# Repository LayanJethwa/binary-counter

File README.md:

# binary-counter

This is a controller board with 3 keys and 3 LEDs, the LEDs display a number from 0-7 in binary, the left key decrements, right key increments, and top key resets the counter.

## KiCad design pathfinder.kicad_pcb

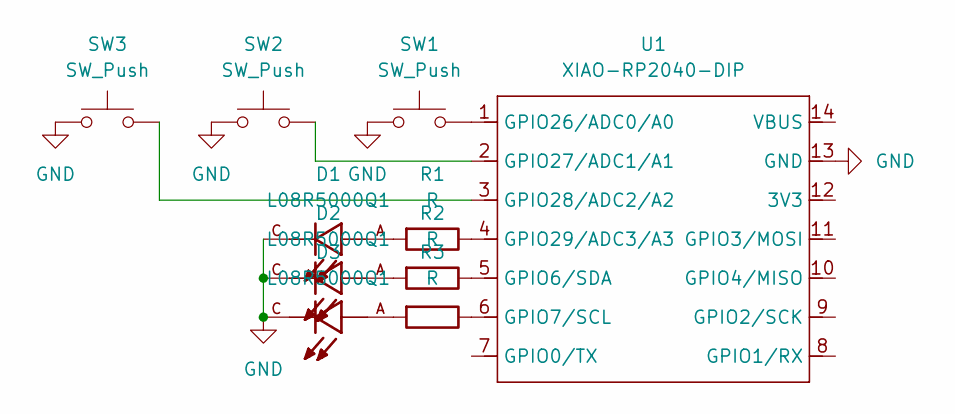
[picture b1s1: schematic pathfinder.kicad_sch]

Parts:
D1, D2, D3: L08R5000Q1; LEDRD254W57D500H1070; PARTREV NA
R1, R2, R3: R; R_Axial_DIN0204_L3.6mm_D1.6mm_P5.08mm_Horizontal
SW1, SW2, SW3: SW_Push; SW_Cherry_MX_1.00u_PCB
U1: XIAO-RP2040-DIP

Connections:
GND: D1.C, D2.C, D3.C, SW1.1, SW2.1, SW3.1, U1.13 (GND)
unnamed: D1.A, R1.2
unnamed: D2.A, R2.2
unnamed: D3.A, R3.2
unnamed: R2.1, U1.5 (GPIO6/SDA)
unnamed: R3.1, U1.6 (GPIO7/SCL)
unnamed: SW1.2, U1.1 (GPIO26/ADC0/A0)
unnamed: SW2.2, U1.2 (GPIO27/ADC1/A1)
unnamed: SW3.2, U1.3 (GPIO28/ADC2/A2)
unnamed: R1.1, U1.4 (GPIO29/ADC3/A3)

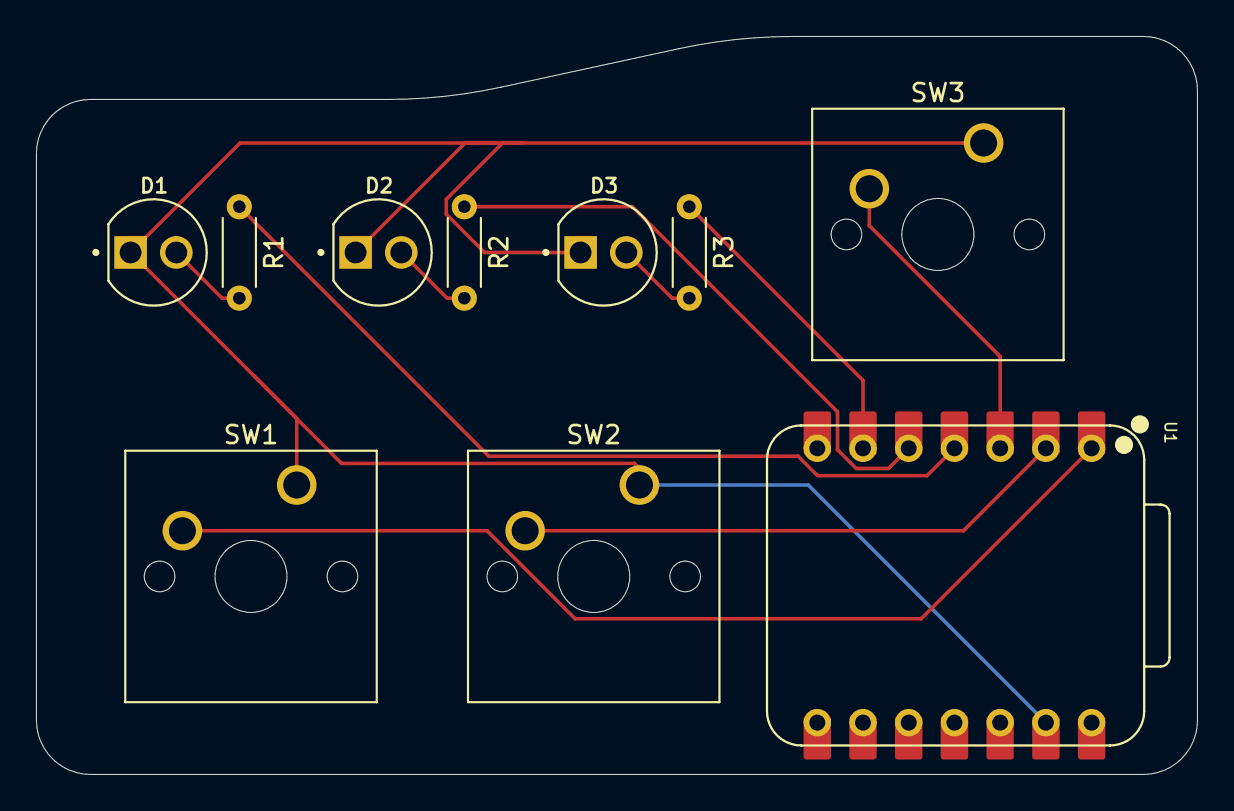
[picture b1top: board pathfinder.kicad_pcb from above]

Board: 2 copper layers, 64.5 x 41.0 mm, 10 parts (0 on the bottom side), 10 nets.

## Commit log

2025-07-30 Add all hardware files
2025-07-30 Rename Screenshot 2025-07-31 002823.png to schematic.png
2025-07-30 Rename Screenshot 2025-07-31 002921.png to pcb.png
2025-07-30 Rename Screenshot 2025-07-31 002930.png to 3d-model.png
